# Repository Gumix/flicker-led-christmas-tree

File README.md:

View this project on [CADLAB.io](https://cadlab.io/node/795). 

# flicker-led-christmas-tree
Flickering LED Christmas Tree

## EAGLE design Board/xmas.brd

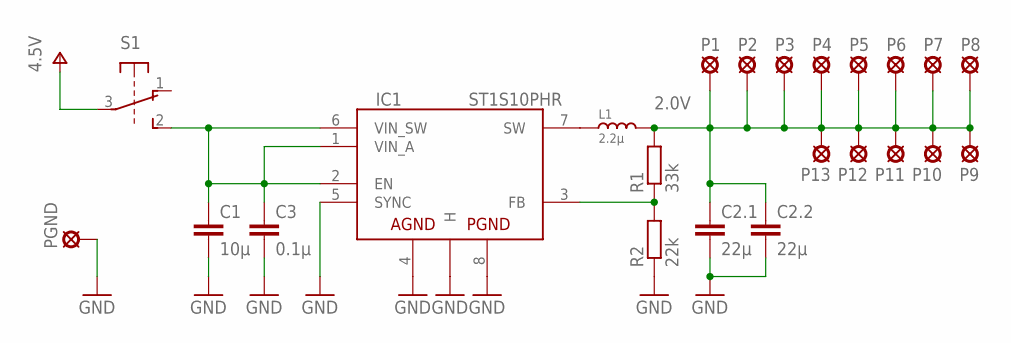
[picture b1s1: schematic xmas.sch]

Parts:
C1: 10μ; C1206
C2.1, C2.2: 22μ; C1206
C3: 0.1μ; C1206
IC1: ST1S10PHR; HSOP8
L1: 2.2μ; L1210W
P1, P2, P3, P4, P5, P6, P7, P8, P9, P10, P11, P12, P13: LSP08
PGND: LSP08
R1: 33k; R1206
R2: 22k; R1206
S1: 9077-2

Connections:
2.0V: C2.1.1, C2.2.1, L1.2, P1.P$1, P2.P$1, P3.P$1, P4.P$1, P5.P$1, P6.P$1, P7.P$1, P8.P$1, P9.P$1, P10.P$1, P11.P$1, P12.P$1, P13.P$1, R1.2
GND: C1.2, C2.1.2, C2.2.2, C3.2, IC1.4 (AGND), IC1.5 (SYNC), IC1.8 (PGND), IC1.H@1 (H), PGND.P$1, R2.1
unnamed: IC1.7 (SW), L1.1
unnamed: IC1.3 (FB), R1.1, R2.2
V+: S1.3
V_IN: C1.1, C3.1, IC1.1 (VIN_A), IC1.2 (EN), IC1.6 (VIN_SW), S1.2 (S)

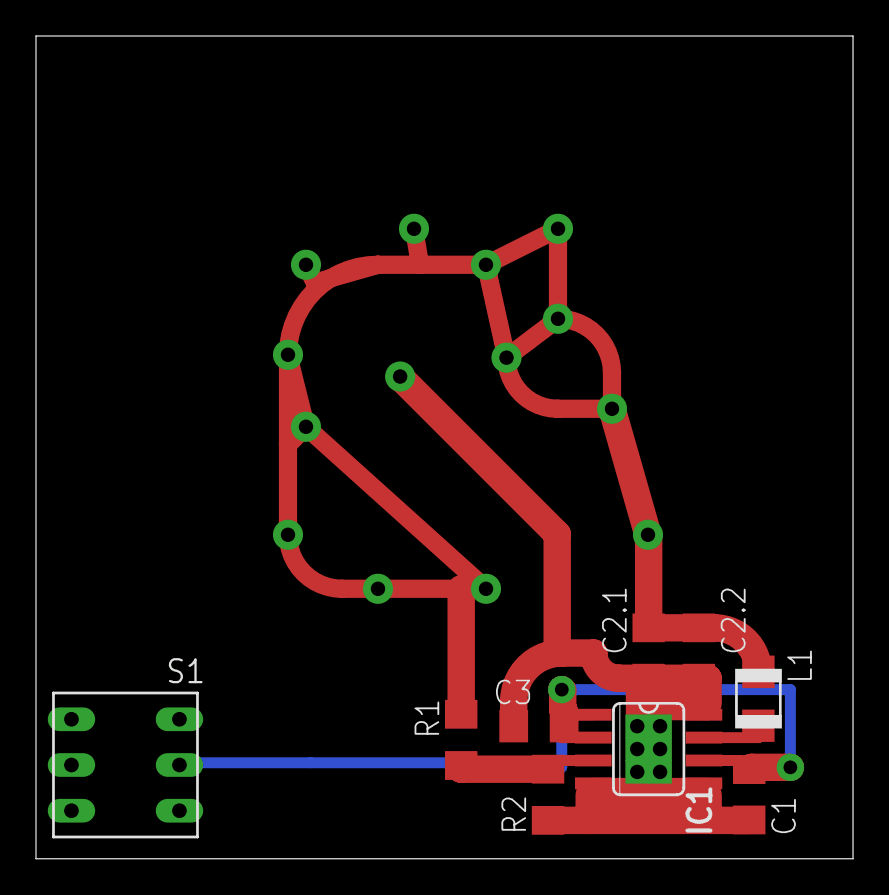
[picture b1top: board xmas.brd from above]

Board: 2 copper layers, 45.4 x 45.7 mm, 23 parts (0 on the bottom side), 5 nets.

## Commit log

2018-03-27 Backlink to CADLAB.io has been added.

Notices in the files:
parts and their libraries:
vreg-pulse: 2009 Draw by Ivan A-R. License CC-BY-SA 3.0
